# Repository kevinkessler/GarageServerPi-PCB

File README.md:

PCBs for the Garage Server Pi Project

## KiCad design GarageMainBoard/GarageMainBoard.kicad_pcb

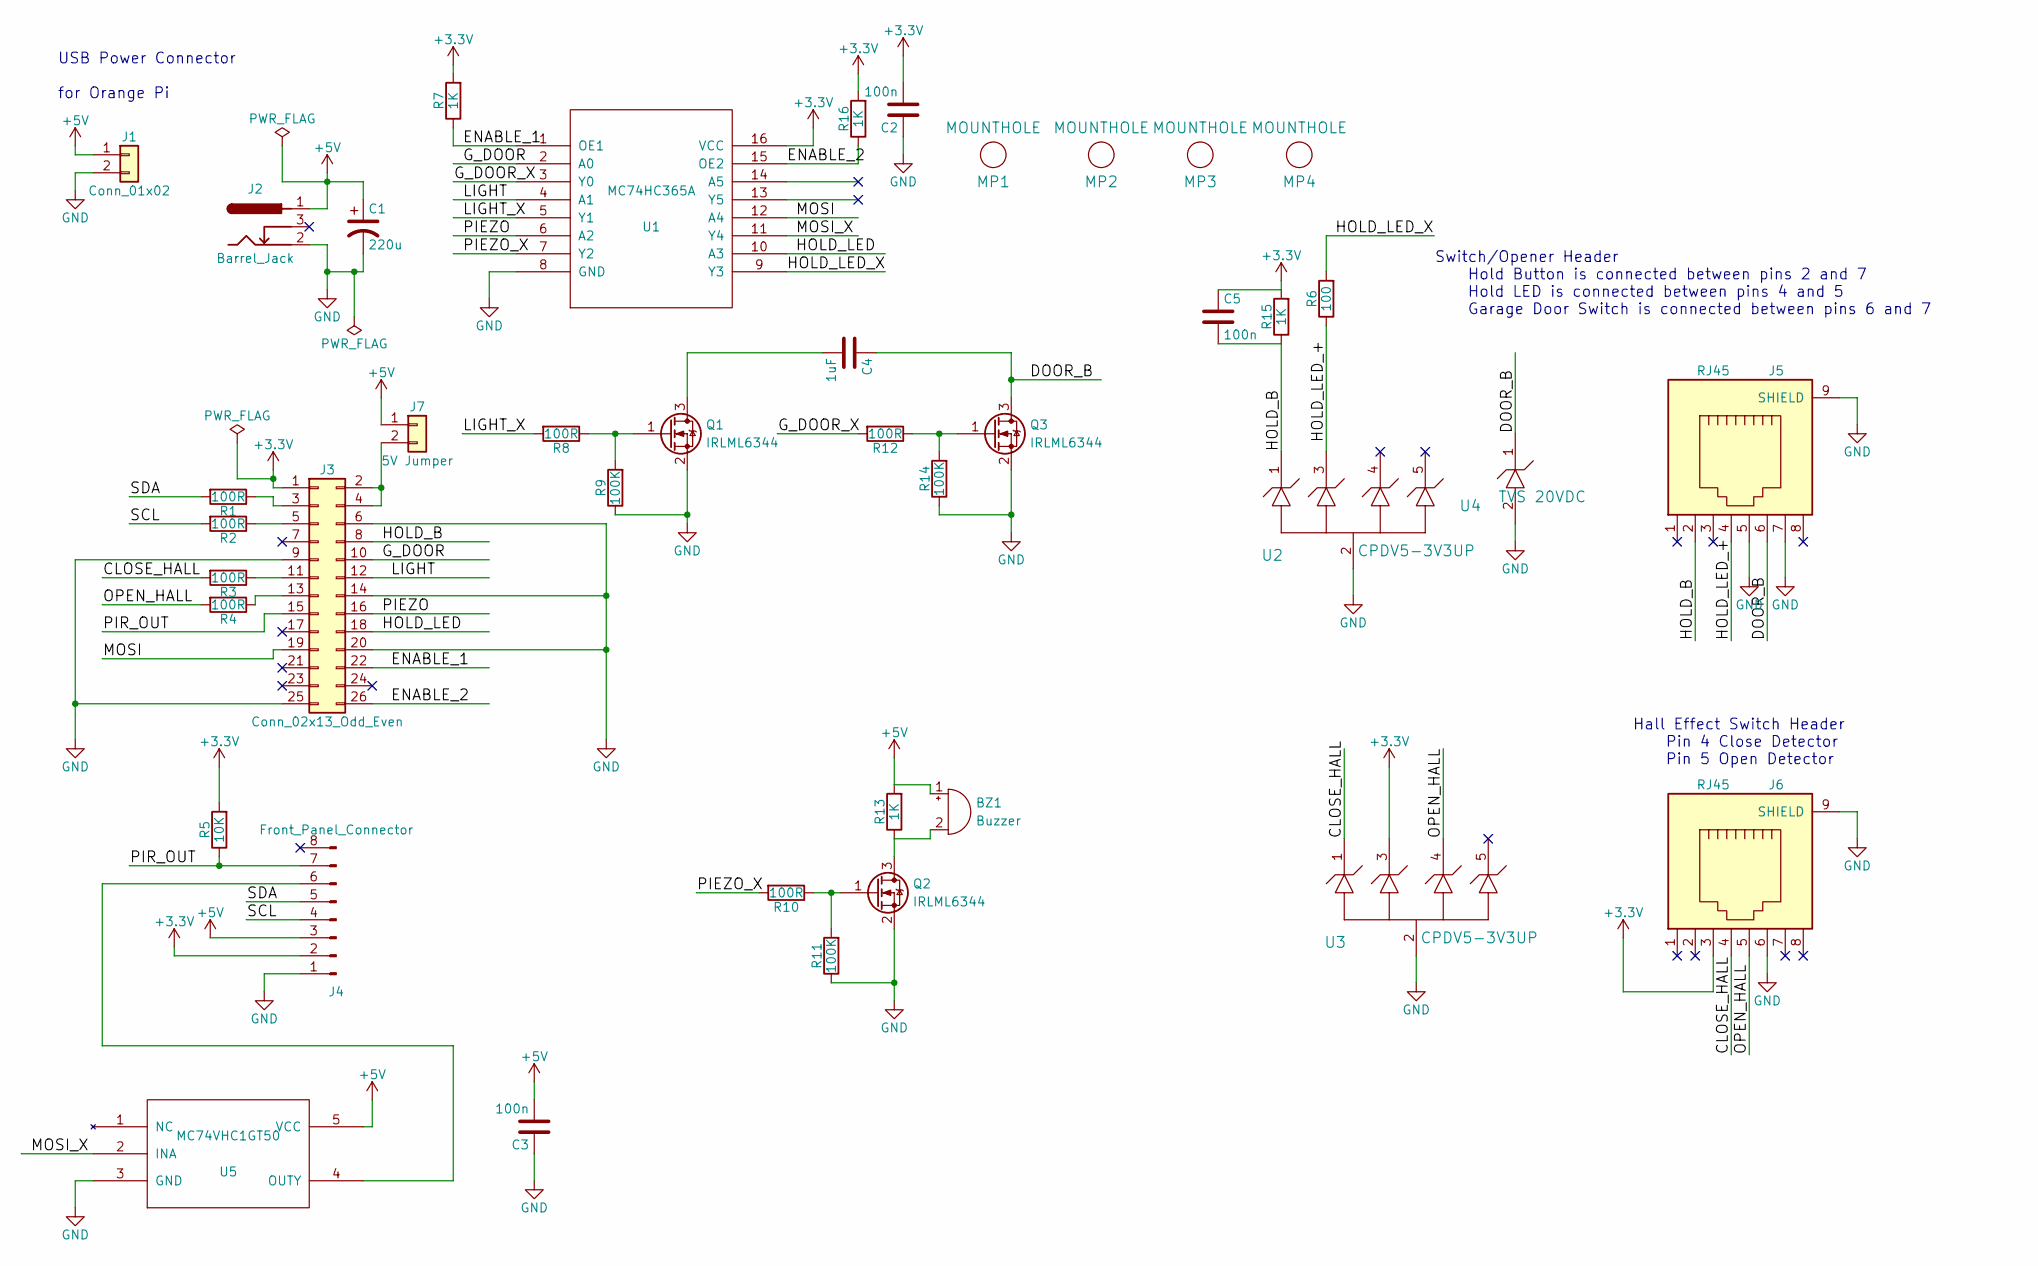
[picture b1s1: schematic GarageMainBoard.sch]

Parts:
BZ1: Buzzer; Buzzer_12x9.5RM7.6
C1: 220u; CP_Radial_D6.3mm_P2.50mm
C2, C3, C5: 100n; C_0805_HandSoldering
C4: 1uF; C_0805_HandSoldering
J1: Conn_01x02; Pin_Header_Straight_1x02_Pitch2.54mm
J2: Barrel_Jack; BARREL_JACK
J3: Conn_02x13_Odd_Even; Pin_Header_Straight_2x13_Pitch2.54mm
J4: Front_Panel_Connector; JST_PH_B8B-PH-K_08x2.00mm_Straight
J5, J6: RJ45; RJ45_LOW_PROFILE_NO_CUT
J7: 5V Jumper; Pin_Header_Straight_1x02_Pitch2.54mm
MP1, MP2, MP3, MP4: MOUNTHOLE; TH-M3
Q1, Q2, Q3: IRLML6344; SOT-23_Handsoldering
R1, R2, R3, R4, R8, R10, R12: 100R; R_0805_HandSoldering
R5: 10K; R_0805_HandSoldering
R6: 100; R_0805_HandSoldering
R7, R13, R15, R16: 1K; R_0805_HandSoldering
R9, R11, R14: 100K; R_0805_HandSoldering
U1: MC74HC365A; SOIC-16_3.9x9.9mm_Pitch1.27mm
U2, U3: CPDV5-3V3UP; SOT-353_SC-70-5_Handsoldering
U4: TVS 20VDC; D_SMB
U5: MC74VHC1GT50; SOT-353_SC-70-5_Handsoldering

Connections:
+3V3: C2.2, C5.1, J3.1, J4.2, J6.3, R5.2, R7.2, R15.2, R16.2, U1.16 (VCC), U3.3
+5V: BZ1.1 (-), C1.1, C3.2, J1.1, J2.1, J4.3, J7.1, R13.2, U5.5 (VCC)
/CLOSE_HALL: J6.4, R3.2, U3.1
/DOOR_B: C4.1, J5.6, Q3.3 (D), U4.1
/ENABLE_1: J3.22, R7.1, U1.1 (OE1)
/ENABLE_2: J3.26, R16.1, U1.15 (OE2)
/G_DOOR: J3.10, U1.2 (A0)
/G_DOOR_X: R12.2, U1.3 (Y0)
/HOLD_B: C5.2, J3.8, J5.2, R15.1, U2.1
/HOLD_LED: J3.18, U1.10 (A3)
/HOLD_LED_+: J5.4, R6.1, U2.3
/HOLD_LED_X: R6.2, U1.9 (Y3)
/LIGHT: J3.12, U1.4 (A1)
/LIGHT_X: R8.2, U1.5 (Y1)
/MOSI: J3.19, U1.12 (A4)
/MOSI_X: U1.11 (Y4), U5.2 (INA)
/OPEN_HALL: J6.5, R4.2, U3.4
/PIEZO: J3.16, U1.6 (A2)
/PIEZO_X: R10.2, U1.7 (Y2)
/PIR_OUT: J3.15, J4.7, R5.1
/SCL: J4.4, R2.2
/SDA: J4.5, R1.2
GND: C1.2, C2.1, C3.1, J1.2, J2.2, J3.6, J3.9, J3.14, J3.20, J3.25, J4.1, J5.5, J5.7, J5.9 (SHIELD), J6.6, J6.9 (SHIELD), Q1.2 (S), Q2.2 (S), Q3.2 (S), R9.1, R11.1, R14.1, U1.8 (GND), U2.2, U3.2, U4.2, U5.3 (GND)
unnamed: BZ1.2 (+), Q2.3 (D), R13.1
unnamed: C4.2, Q1.3 (D)
unnamed: J3.2, J3.4, J7.2
unnamed: J3.3, R1.1
unnamed: J3.5, R2.1
unnamed: J3.11, R3.1
unnamed: J3.13, R4.1
unnamed: J4.6, U5.4 (OUTY)
unnamed: Q1.1 (G), R8.1, R9.2
unnamed: Q2.1 (G), R10.1, R11.2
unnamed: Q3.1 (G), R12.1, R14.2

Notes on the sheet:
Switch/Opener Header Hold Button is connected between pins 2 and 7 Hold LED is connected between pins 4 and 5 Garage Door Switch is connected between pins 6 and 7
Hall Effect Switch Header Pin 4 Close Detector Pin 5 Open Detector
USB Power Connector for Orange Pi

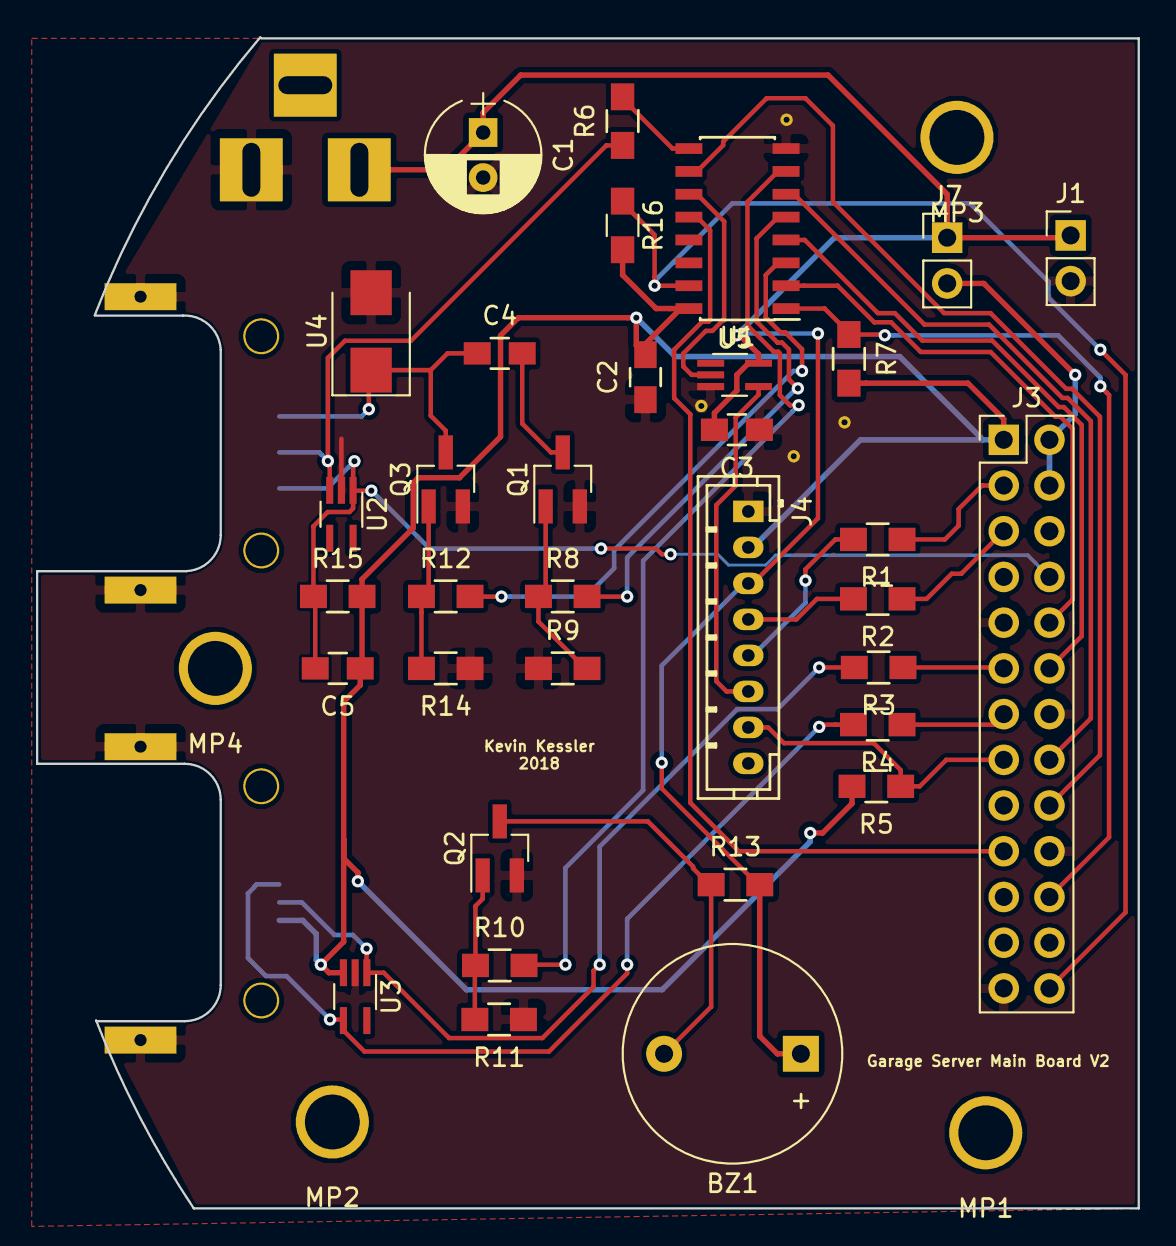
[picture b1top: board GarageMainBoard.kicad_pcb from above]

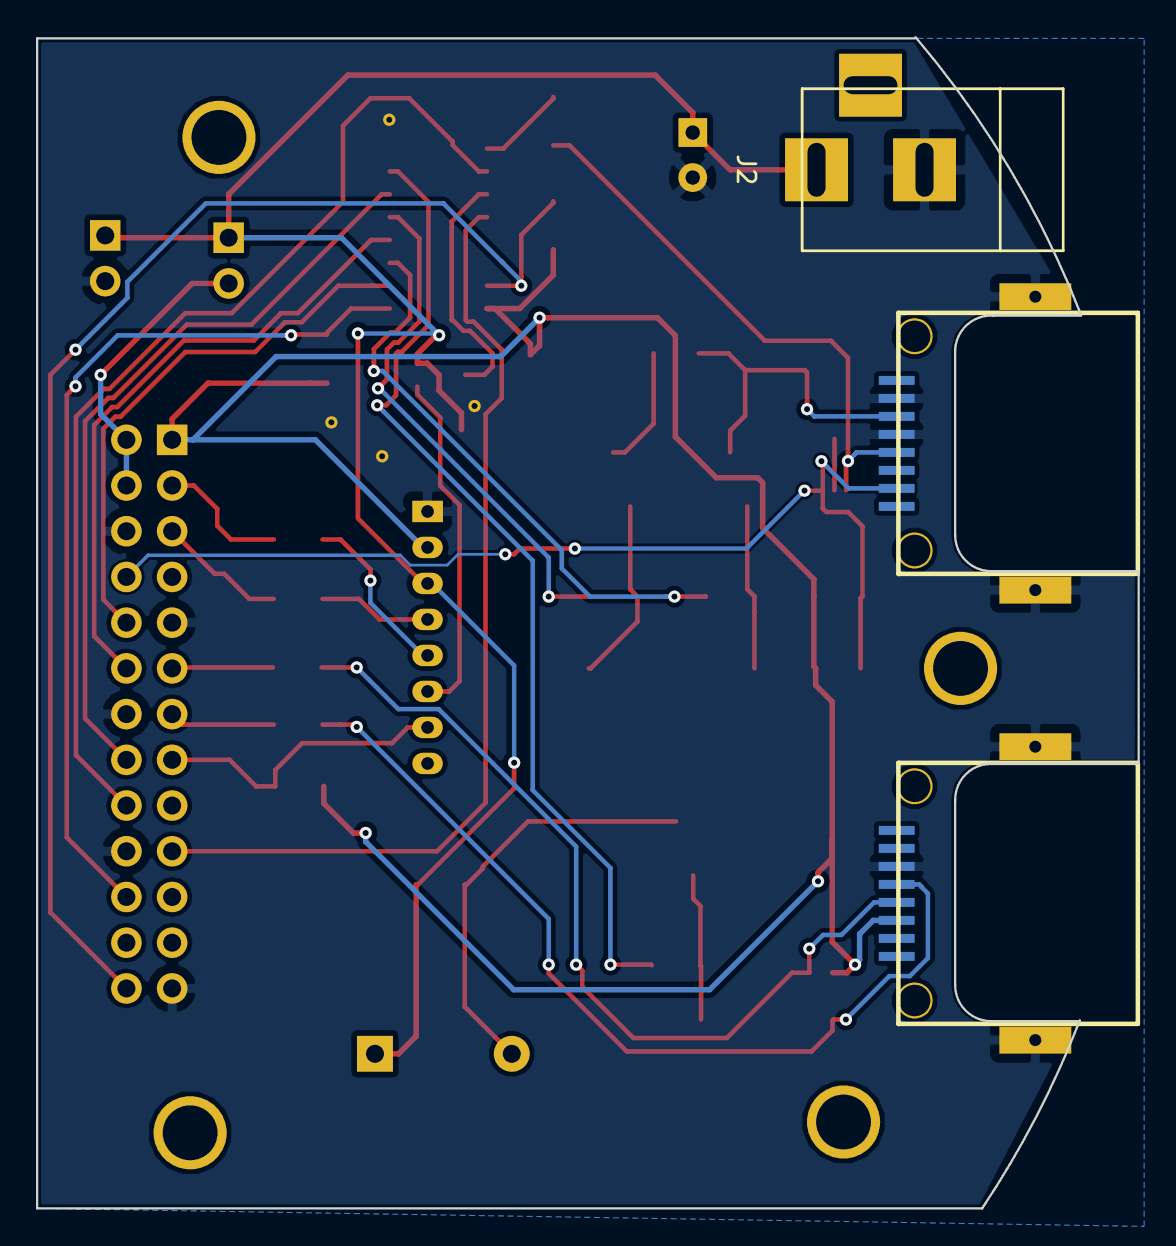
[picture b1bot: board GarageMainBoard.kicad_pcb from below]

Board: 2 copper layers, 61.2 x 65.1 mm, 41 parts (3 on the bottom side), 34 nets.

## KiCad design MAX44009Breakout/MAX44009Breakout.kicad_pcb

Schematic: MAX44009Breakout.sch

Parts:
C1: 1u; C_0805_HandSoldering
P1: CONN_01X06; JST_SH_6_PIN
U1: MAX44009

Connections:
/GND: C1.1, P1.2, U1.2 (GND)
unnamed: C1.2, P1.1, U1.1 (VCC)
unnamed: P1.3, U1.3 (A0)
unnamed: P1.4, U1.4 (~INT)
unnamed: P1.5, U1.5 (SCL)
unnamed: P1.6, U1.6 (SDA)

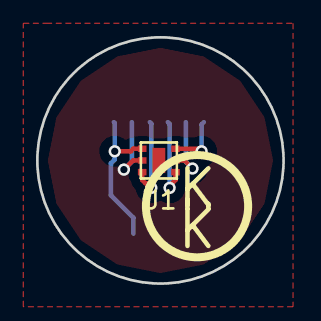
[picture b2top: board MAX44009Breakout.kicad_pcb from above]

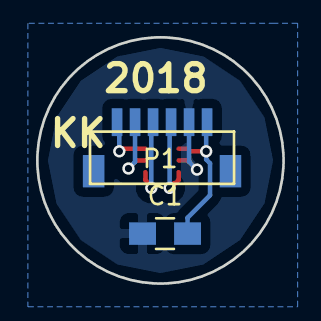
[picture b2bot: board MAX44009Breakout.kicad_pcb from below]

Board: 2 copper layers, 13.7 x 13.7 mm, 3 parts (2 on the bottom side), 6 nets.

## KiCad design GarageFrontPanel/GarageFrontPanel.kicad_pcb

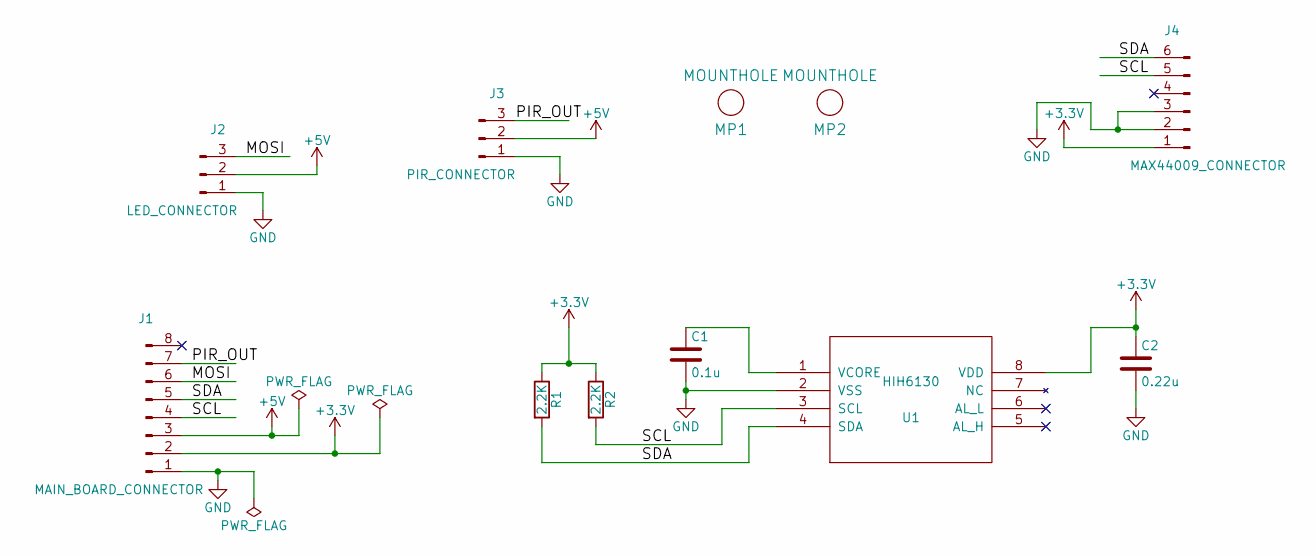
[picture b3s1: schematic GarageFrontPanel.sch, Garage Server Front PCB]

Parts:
C1: 0.1u; C_0805_HandSoldering
C2: 0.22u; C_0805_HandSoldering
J1: MAIN_BOARD_CONNECTOR; JST_PH_B8B-PH-K_08x2.00mm_Straight
J2: LED_CONNECTOR; JST_PH_B3B-PH-K_03x2.00mm_Straight
J3: PIR_CONNECTOR; JST_PH_B3B-PH-K_03x2.00mm_Straight
J4: MAX44009_CONNECTOR; JST_PH_B6B-PH-K_06x2.00mm_Straight
MP1, MP2: MOUNTHOLE; TH-M3
R1, R2: 2.2K; R_0805_HandSoldering
U1: HIH6130; SOIC-8_3.9x4.9mm_Pitch1.27mm

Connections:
+3V3: C2.1, J1.2, J4.1, R1.1, R2.1, U1.8 (VDD)
+5V: J1.3, J2.2, J3.2
/MOSI: J1.6, J2.3
/PIR_OUT: J1.7, J3.3
/SCL: J1.4, J4.5, R2.2, U1.3 (SCL)
/SDA: J1.5, J4.6, R1.2, U1.4 (SDA)
GND: C1.2, C2.2, J1.1, J2.1, J3.1, J4.2, J4.3, U1.2 (VSS)
unnamed: C1.1, U1.1 (VCORE)

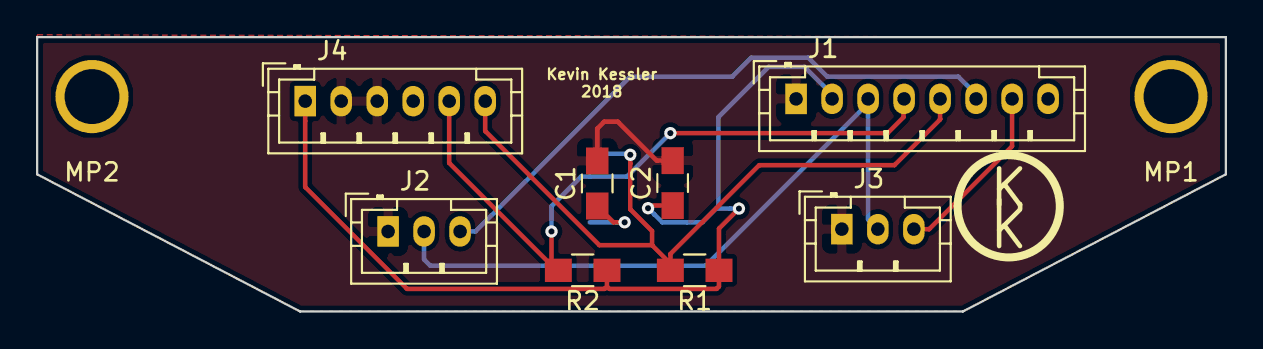
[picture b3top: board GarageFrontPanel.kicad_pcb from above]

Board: 2 copper layers, 66.0 x 15.2 mm, 11 parts (1 on the bottom side), 8 nets.

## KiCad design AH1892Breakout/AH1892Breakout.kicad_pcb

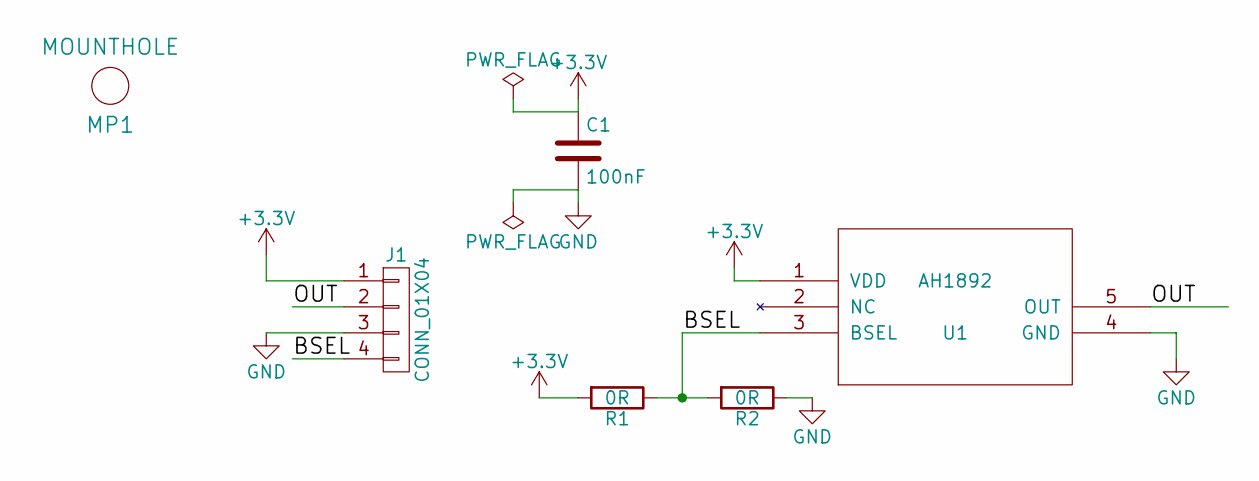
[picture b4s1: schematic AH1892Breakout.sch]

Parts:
C1: 100nF; R_0805_HandSoldering
J1: CONN_01X04; JST_PH_B4B-PH-SM4-TB_04x2.00mm_Straight
MP1: MOUNTHOLE; TH-M3
R1, R2: 0R; R_1206_HandSoldering
U1: AH1892

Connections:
+3V3: C1.1, J1.1, R1.2, U1.1 (VDD)
/BSEL: J1.4, R1.1, R2.2, U1.3 (BSEL)
/OUT: J1.2, U1.5 (OUT)
GND: C1.2, J1.3, R2.1, U1.4 (GND)

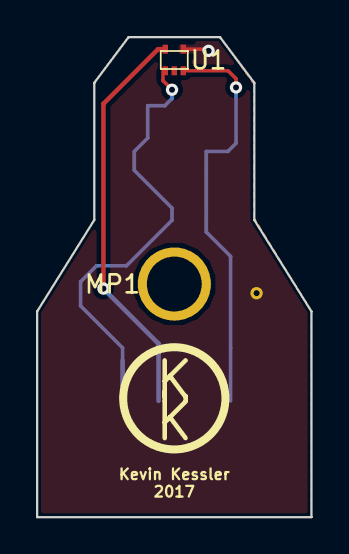
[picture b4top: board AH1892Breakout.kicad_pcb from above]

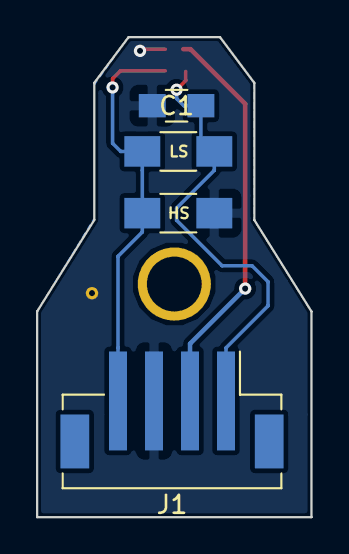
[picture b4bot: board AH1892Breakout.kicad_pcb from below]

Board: 2 copper layers, 15.2 x 26.7 mm, 6 parts (4 on the bottom side), 4 nets.

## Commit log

2018-01-18 Add PDFs
2018-02-07 Main PCB start
2018-02-07 Main PCB
2018-02-08 Flip Main PCB
2018-04-06 Main Board V2
2018-04-07 Pull Ups on 365
2018-04-07 PCB V2
